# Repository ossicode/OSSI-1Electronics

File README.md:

### OSSI-1 Satellite Electronics Final Version 
#### Launched on 19th April 2013

**Check for modules for images, schematics, and BOMs.**

Mainly Eagle 6.1 / 6.5 version  
Please, see the comments from the schematic file for more information.  
Block diagram and rationale behind the design will be provided with video turorial soon.  

Open Source Satellite Initiative http://opensat.cc

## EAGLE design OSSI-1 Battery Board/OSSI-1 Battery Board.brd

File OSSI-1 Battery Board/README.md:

### OSSI-1 Satellite Battery Board

**The battery board contains Saft 144350 lithium-ion battery and two Nesscap supercapacitors.**  
**2 analog out temperature modules are attached to the battery and the supercapacitor for temp. monitoring.**

Mainly Eagle 6.1 / 6.5 version  
Please, see the comments from the schematic file for more information.  
Block diagram and rationale behind the design will be provided with video turorial soon.  

Open Source Satellite Initiative http://opensat.cc

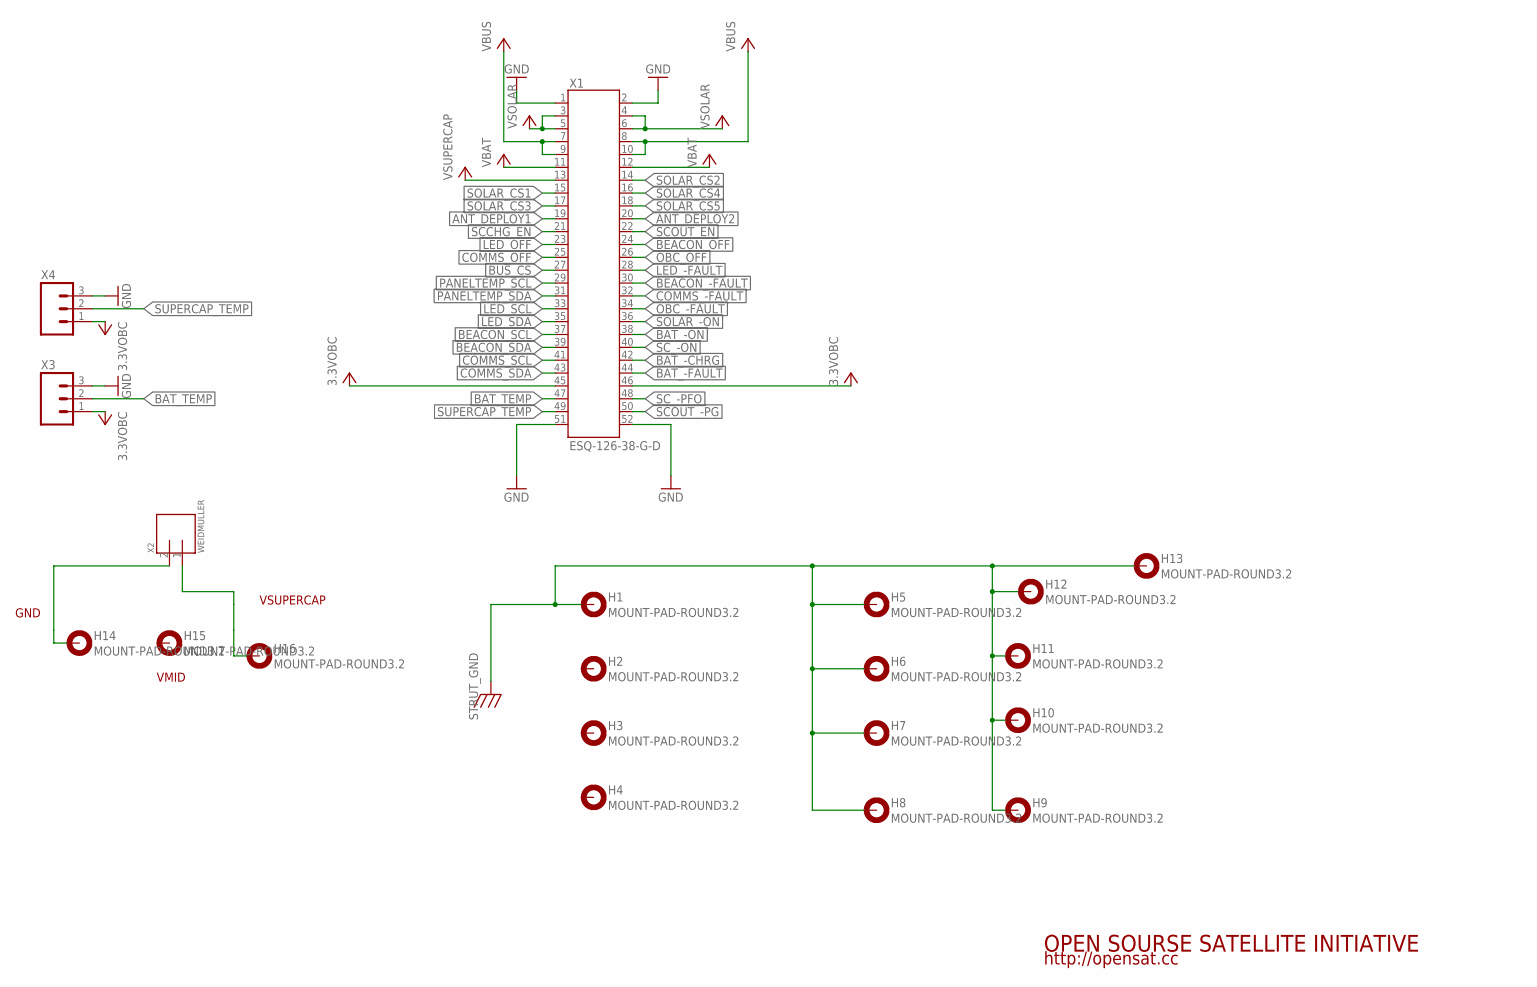
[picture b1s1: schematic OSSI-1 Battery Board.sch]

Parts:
H1, H2, H3, H4, H5, H6, H7, H8, H9, H10, H11, H12, H13, H14, H15, H16: MOUNT-PAD-ROUND3.2; 3.2-PAD-ROUND
X1: ESQ-126-38-G-D; ESQ-126-XX-X-D
X2: WEIDMULLER; WEIDMULLER1760490000
X3, X4: M03PTH; 1X03

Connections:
3.3VOBC: X1.45, X1.46, X3.1, X4.1
ANT_DEPLOY1: X1.19
ANT_DEPLOY2: X1.20
BAT_-CHRG: X1.42
BAT_-FAULT: X1.44
BAT_-ON: X1.38
BAT_TEMP: X1.47, X3.2
BEACON_-FAULT: X1.30
BEACON_OFF: X1.24
BEACON_SCL: X1.37
BEACON_SDA: X1.39
BUS_CS: X1.27
COMMS_-FAULT: X1.32
COMMS_OFF: X1.25
COMMS_SCL: X1.41
COMMS_SDA: X1.43
GND: X1.1, X1.2, X1.51, X1.52, X3.3, X4.3
LED_-FAULT: X1.28
LED_OFF: X1.23
LED_SCL: X1.33
LED_SDA: X1.35
unnamed: H14.B3,2, X2.2
unnamed: H16.B3,2, X2.1
OBC_-FAULT: X1.34
OBC_OFF: X1.26
PANELTEMP_SCL: X1.29
PANELTEMP_SDA: X1.31
SCCHG_EN: X1.21
SCOUT_-PG: X1.50
SCOUT_EN: X1.22
SC_-ON: X1.40
SC_-PFO: X1.48
SOLAR_-ON: X1.36
SOLAR_CS1: X1.15
SOLAR_CS2: X1.14
SOLAR_CS3: X1.17
SOLAR_CS4: X1.16
SOLAR_CS5: X1.18
STRUT_GND: H1.B3,2, H5.B3,2, H6.B3,2, H7.B3,2, H8.B3,2, H9.B3,2, H10.B3,2, H11.B3,2, H12.B3,2, H13.B3,2
SUPERCAP_TEMP: X1.49, X4.2
VBAT: X1.11, X1.12
VBUS: X1.7, X1.8, X1.9, X1.10
VSOLAR: X1.3, X1.4, X1.5, X1.6
VSUPERCAP: X1.13

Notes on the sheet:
GND
VSUPERCAP
VMID
OPEN SOURSE SATELLITE INITIATIVE
http://opensat.cc

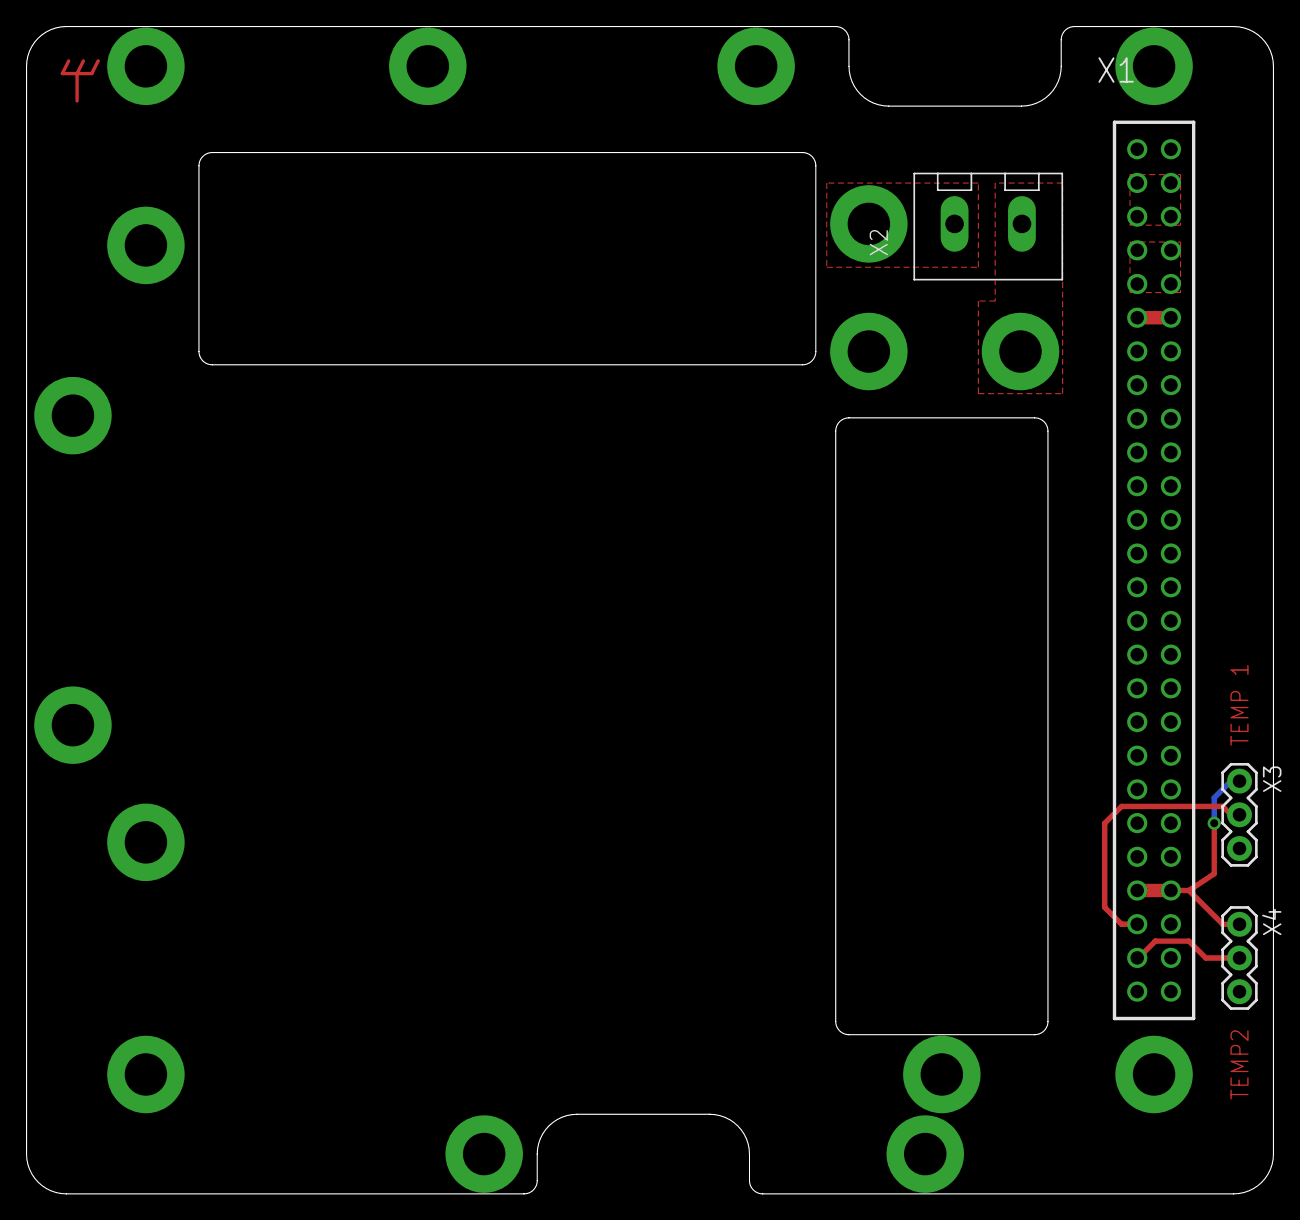
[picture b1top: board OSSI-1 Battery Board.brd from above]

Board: 2 copper layers, 94.0 x 88.0 mm, 20 parts (0 on the bottom side), 10 nets.

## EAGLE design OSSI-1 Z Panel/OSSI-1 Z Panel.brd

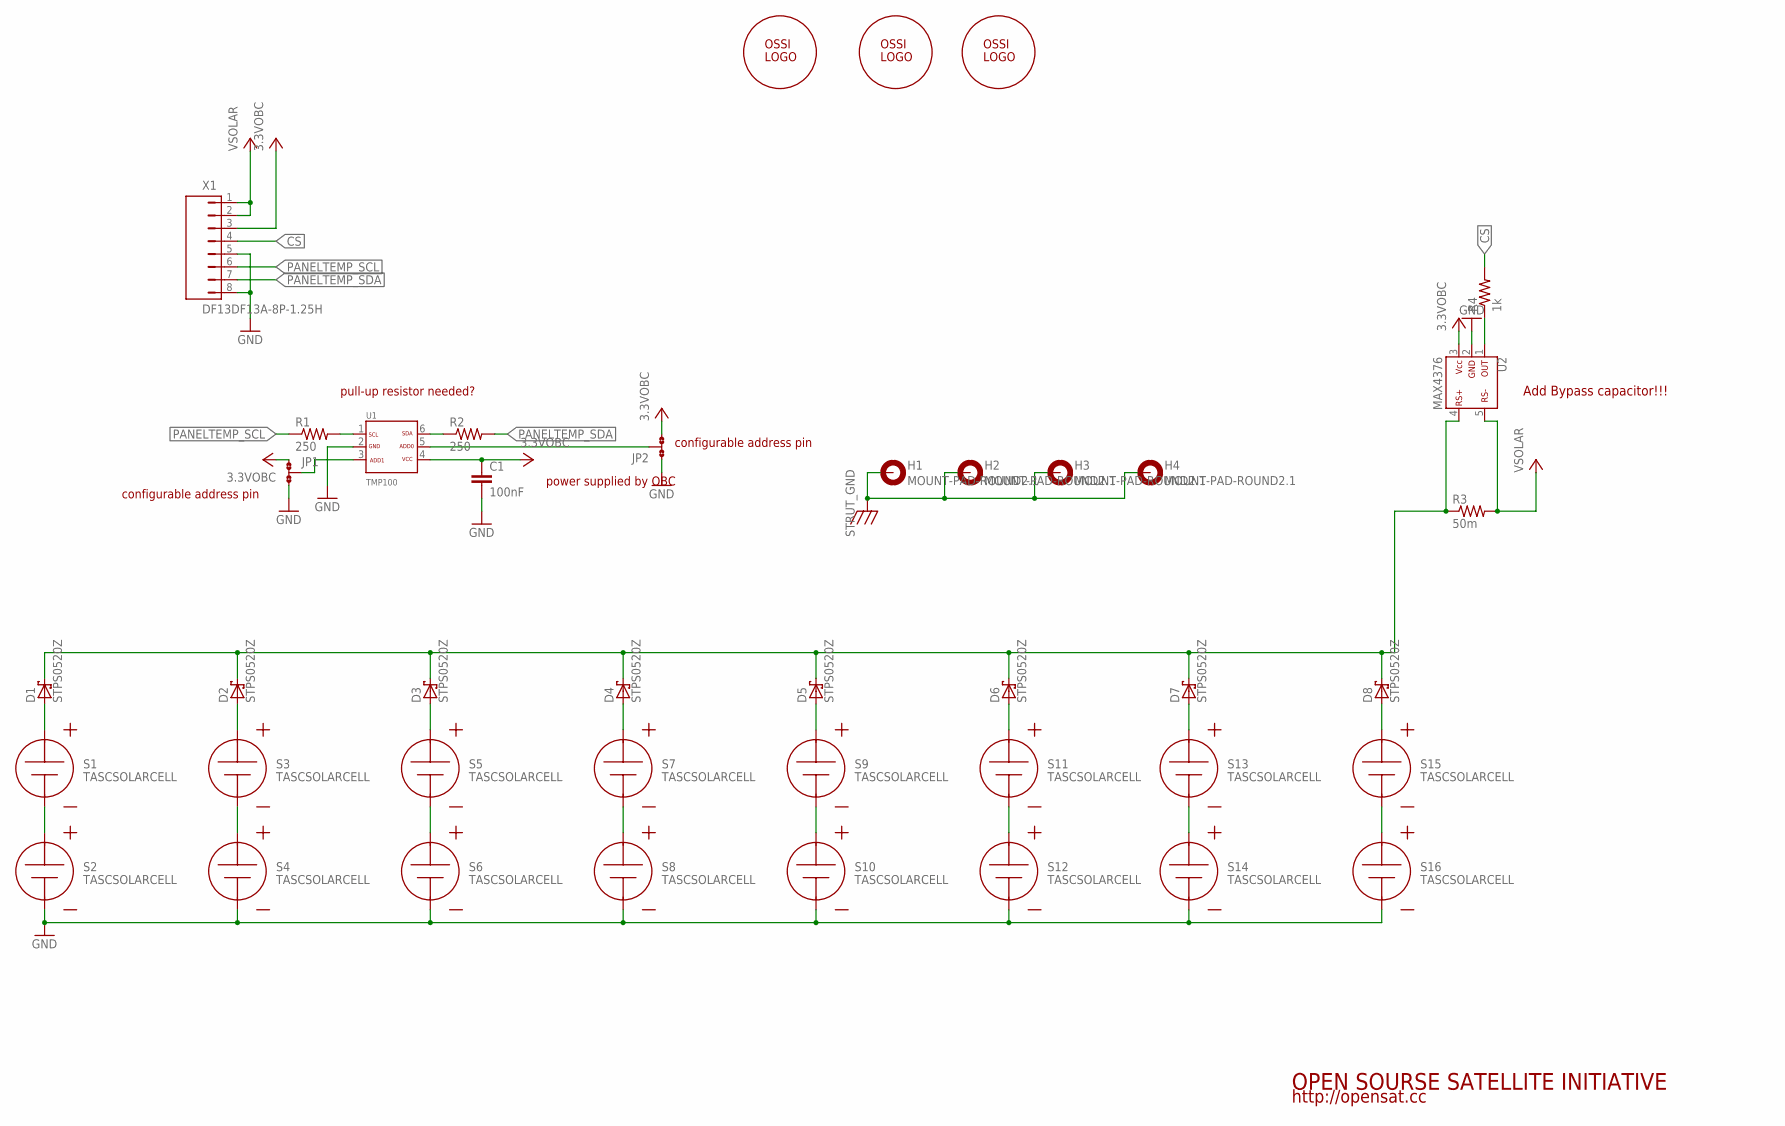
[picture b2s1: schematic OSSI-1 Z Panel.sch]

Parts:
C1: 100nF; C0603(1608)
D1, D2, D3, D4, D5, D6, D7, D8: STPS0520Z; SOD-123
H1, H2, H3, H4: MOUNT-PAD-ROUND2.1; 2.1-PAD-ROUND
JP1, JP2: JP2; JP2SMD0603
R1, R2: 250; R0603(1608)
R3: 50m; WSL1206
R4: 1k; R0603(1608)
S1, S2, S3, S4, S5, S6, S7, S8, S9, S10, S11, S12, S13, S14, S15, S16: TASCSOLARCELL
U1: TMP100; SOT23-6DBV
U2: MAX4376; SOT23-5DBV
U$1, U$2: OSSILOGO-10; OSSILOGO1010
U$3: OSSITAGCC; CCLOGO
X1: DF13DF13A-8P-1.25H; DF13A-8P

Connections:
3.3VOBC: C1.1, JP1.1, JP2.3, U1.4, U2.3, X1.3
CS: R4.2, X1.4
GND: C1.2, JP1.3, JP2.1, S2.N, S4.N, S6.N, S8.N, S10.N, S12.N, S14.N, S16.N, U1.2, U2.2, X1.5, X1.8
unnamed: S1.N, S2.P
unnamed: D1.A, S1.P
unnamed: S3.N, S4.P
unnamed: D2.A, S3.P
unnamed: S5.N, S6.P
unnamed: D3.A, S5.P
unnamed: S7.N, S8.P
unnamed: D4.A, S7.P
unnamed: S9.N, S10.P
unnamed: D5.A, S9.P
unnamed: S11.N, S12.P
unnamed: D6.A, S11.P
unnamed: S13.N, S14.P
unnamed: D7.A, S13.P
unnamed: S15.N, S16.P
unnamed: D8.A, S15.P
unnamed: R1.2, U1.1
unnamed: R2.1, U1.6
unnamed: D1.C, D2.C, D3.C, D4.C, D5.C, D6.C, D7.C, D8.C, R3.P$1 (1), U2.4
unnamed: JP1.2, U1.3
unnamed: JP2.2, U1.5
unnamed: R4.1, U2.1
PANELTEMP_SCL: R1.1, X1.6
PANELTEMP_SDA: R2.2, X1.7
STRUT_GND: H1.B3,2, H2.B3,2, H3.B3,2, H4.B3,2
VSOLAR: R3.P$2 (2), U2.5, X1.1, X1.2

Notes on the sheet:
configurable address pin
pull-up resistor needed?
power supplied by OBC
Add Bypass capacitor!!!
OPEN SOURSE SATELLITE INITIATIVE
http://opensat.cc

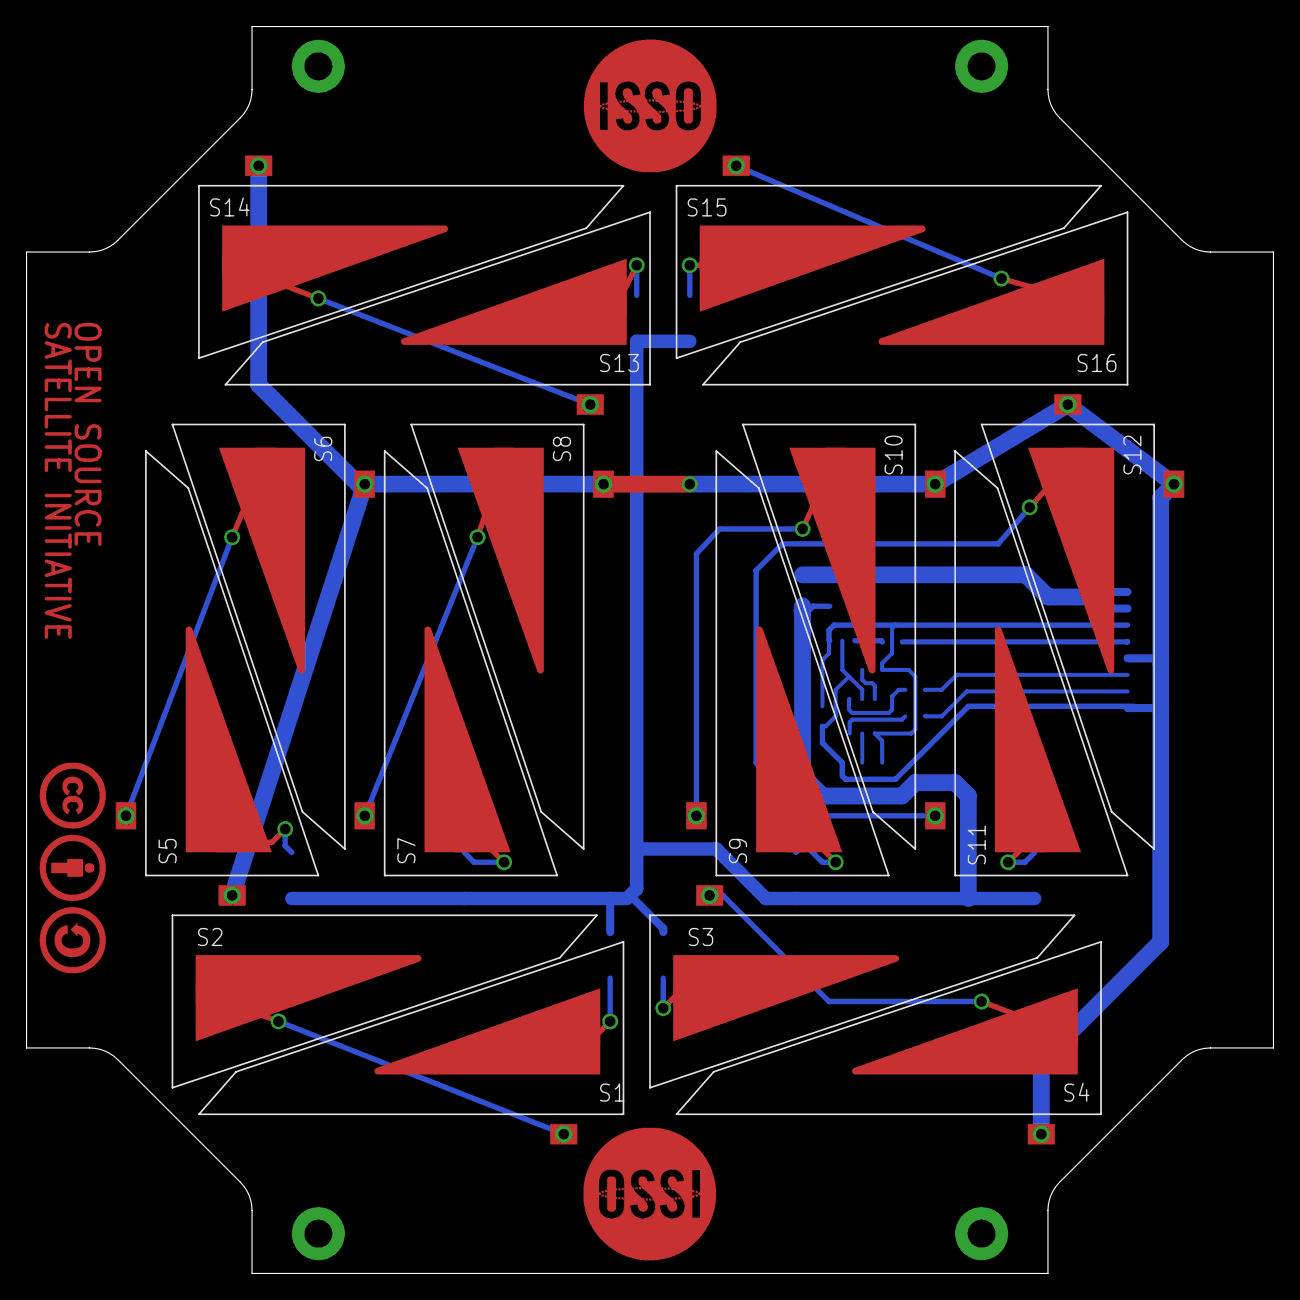
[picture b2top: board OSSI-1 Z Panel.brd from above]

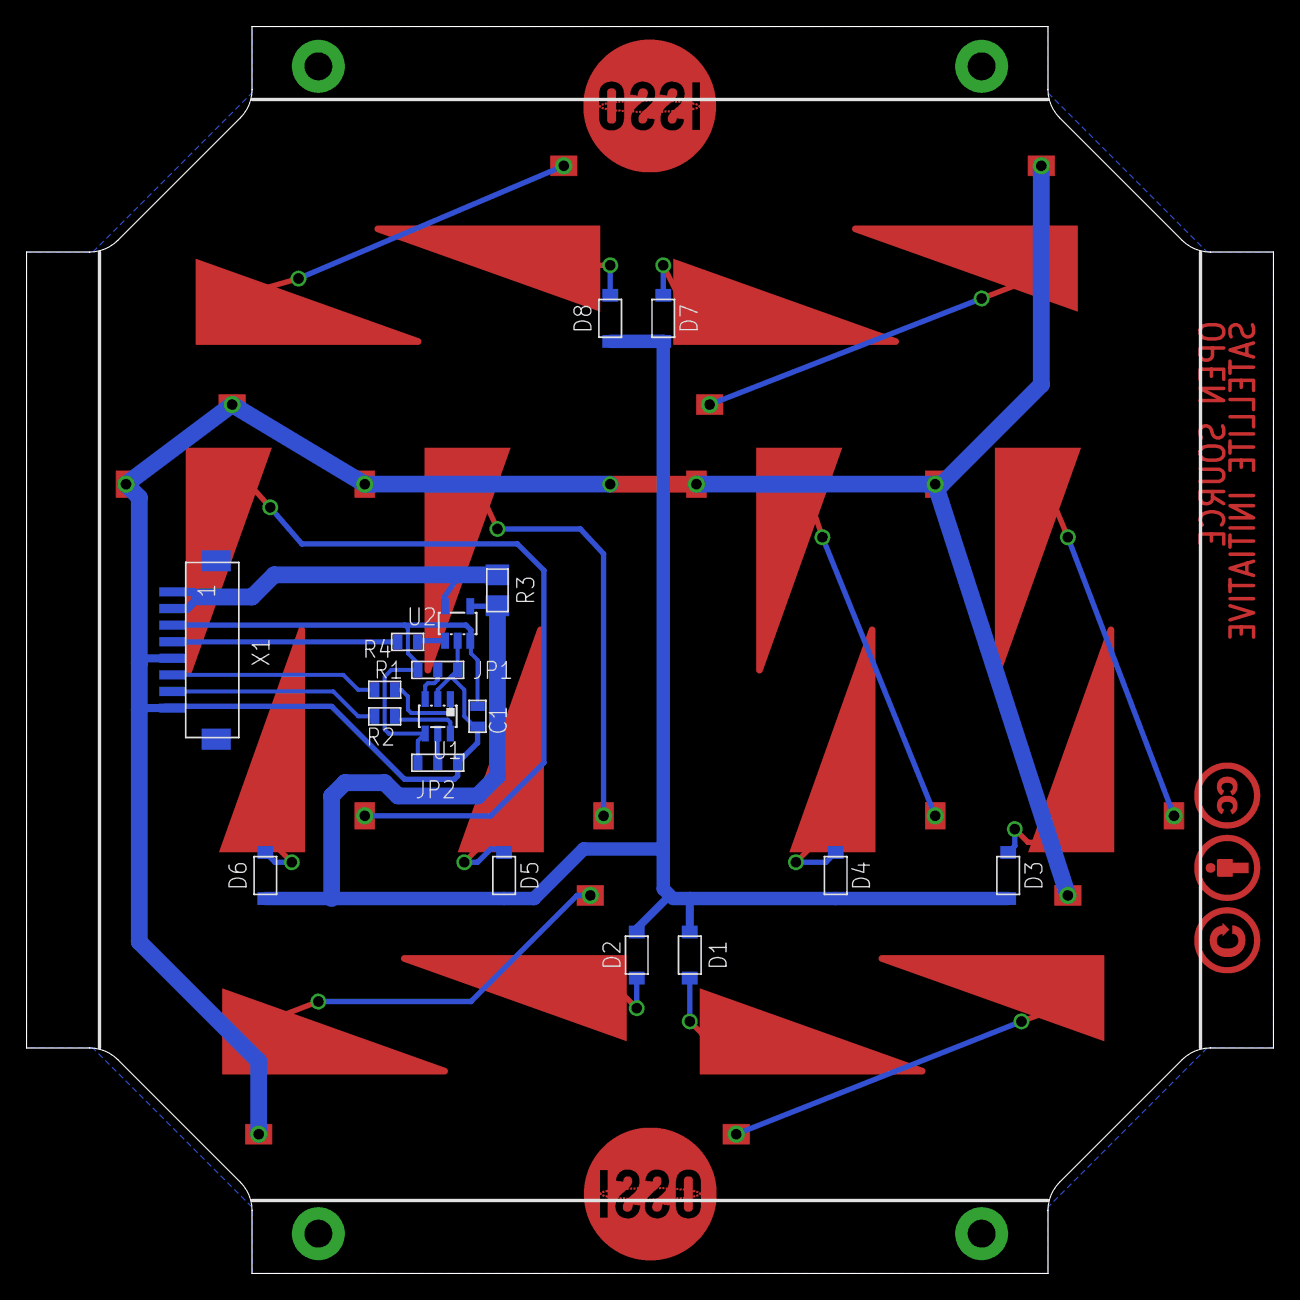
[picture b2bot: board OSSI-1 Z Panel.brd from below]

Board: 2 copper layers, 94.0 x 94.0 mm, 41 parts (18 on the bottom side), 29 nets.

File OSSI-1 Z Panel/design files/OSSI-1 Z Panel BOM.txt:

Part	Value	Attributes	Package	Description	Part Num
C1	100nF		C0603(1608)		*
D1	STPS0520Z		SOD-123	We use STPS0520Z by st.com diode for solar cell schottky diode.	*
D2	STPS0520Z		SOD-123	We use STPS0520Z by st.com diode for solar cell schottky diode.	*
D3	STPS0520Z		SOD-123	We use STPS0520Z by st.com diode for solar cell schottky diode.	*
D4	STPS0520Z		SOD-123	We use STPS0520Z by st.com diode for solar cell schottky diode.	*
D5	STPS0520Z		SOD-123	We use STPS0520Z by st.com diode for solar cell schottky diode.	*
D6	STPS0520Z		SOD-123	We use STPS0520Z by st.com diode for solar cell schottky diode.	*
D7	STPS0520Z		SOD-123	We use STPS0520Z by st.com diode for solar cell schottky diode.	*
D8	STPS0520Z		SOD-123	We use STPS0520Z by st.com diode for solar cell schottky diode.	*
H1	MOUNT-PAD-ROUND2.1		2.1-PAD-ROUND		*
H2	MOUNT-PAD-ROUND2.1		2.1-PAD-ROUND		*
H3	MOUNT-PAD-ROUND2.1		2.1-PAD-ROUND		*
H4	MOUNT-PAD-ROUND2.1		2.1-PAD-ROUND		*
JP1	JP2		JP2SMD0603		*
JP2	JP2		JP2SMD0603		*
R1	250		R0603(1608)		*
R2	250		R0603(1608)		*
R3	50m		WSL1206		*
R4	1k		R0603(1608)		*
S1	TASCSOLARCELL		TASCSOLARCELL		*
S2	TASCSOLARCELL		TASCSOLARCELL		*
S3	TASCSOLARCELL		TASCSOLARCELL		*
S4	TASCSOLARCELL		TASCSOLARCELL		*
S5	TASCSOLARCELL		TASCSOLARCELL		*
S6	TASCSOLARCELL		TASCSOLARCELL		*
S7	TASCSOLARCELL		TASCSOLARCELL		*
S8	TASCSOLARCELL		TASCSOLARCELL		*
S9	TASCSOLARCELL		TASCSOLARCELL		*
S10	TASCSOLARCELL		TASCSOLARCELL		*
S11	TASCSOLARCELL		TASCSOLARCELL		*
S12	TASCSOLARCELL		TASCSOLARCELL		*
S13	TASCSOLARCELL		TASCSOLARCELL		*
S14	TASCSOLARCELL		TASCSOLARCELL		*
S15	TASCSOLARCELL		TASCSOLARCELL		*
S16	TASCSOLARCELL		TASCSOLARCELL		*
U$1	OSSILOGO-10		OSSILOGO1010		*
U$2	OSSILOGO-10		OSSILOGO1010		*
U$3	OSSITAGCC		CCLOGO		*
U1	TMP100		SOT23-6DBV	TMP100 Digital Temerature Sensor with I2C Interface from Texas Instruments	*
U2	MAX4376		SOT23-5DBV		*
X1	DF13DF13A-8P-1.25H		DF13A-8P	Hirose DF13 series connector	*

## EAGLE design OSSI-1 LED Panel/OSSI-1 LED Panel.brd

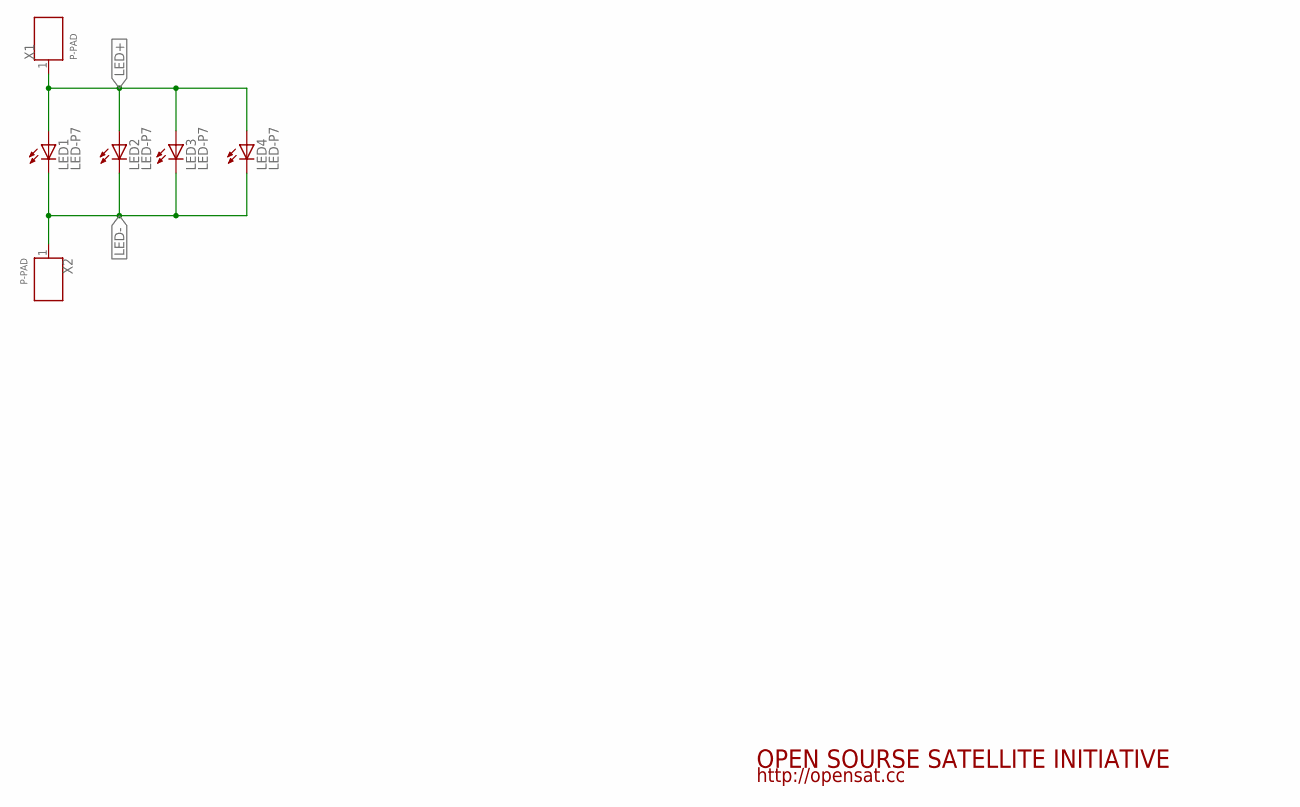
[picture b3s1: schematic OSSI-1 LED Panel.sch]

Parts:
LED1, LED2, LED3, LED4: LED-P7; P7
X1, X2: P-PAD

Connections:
LED+: LED1.A, LED2.A, LED3.A, LED4.A, X1.1
LED-: LED1.C, LED2.C, LED3.C, LED4.C, X2.1

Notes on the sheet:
OPEN SOURSE SATELLITE INITIATIVE
http://opensat.cc

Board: 2 copper layers, 6 parts (0 on the bottom side), 2 nets, no tracks yet.

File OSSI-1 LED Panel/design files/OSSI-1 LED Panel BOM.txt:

Part	Value	Attributes	Package	Description	Part Num
LED1	LED-P7		P7		*
LED2	LED-P7		P7		*
LED3	LED-P7		P7		*
LED4	LED-P7		P7		*
X1	P-PAD		P-PAD		*
X2	P-PAD		P-PAD		*

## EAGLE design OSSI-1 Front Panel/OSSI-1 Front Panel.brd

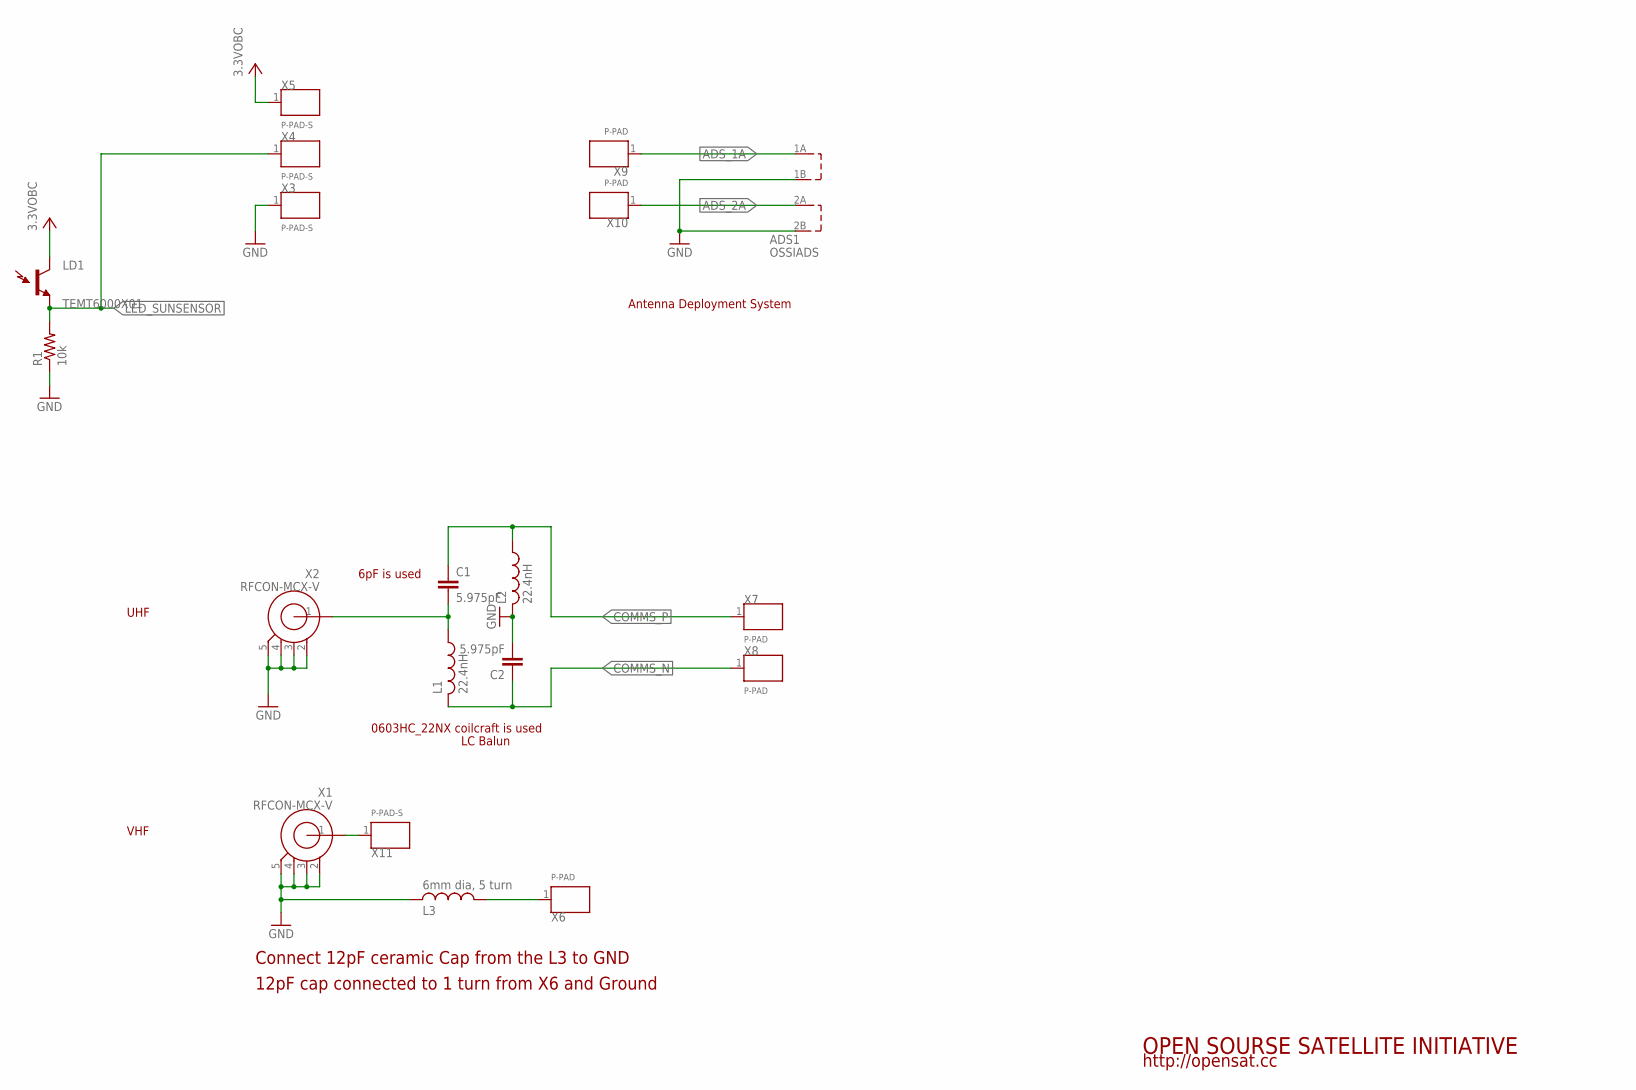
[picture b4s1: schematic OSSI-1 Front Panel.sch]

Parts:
ADS1: OSSIADS
C1, C2: 5.975pF; C0805(2012)
L1, L2: 22.4nH; L0805(2012)
L3: 6mm dia, 5 turn; 0207/10
LD1: TEMT6000X01; TEMT6000-SEN
R1: 10k; R0805(2012)
X1, X2: RFCON-MCX-V; MCX-V
X3, X4, X5, X11: P-PAD-S
X6, X7, X8, X9, X10: P-PAD

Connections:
3.3VOBC: LD1.COLLECTOR (C1), X5.1
ADS_1A: ADS1.1A, X9.1
ADS_2A: ADS1.2A, X10.1
COMMS_N: C2.1, L1.2, X8.1
COMMS_P: C1.1, L2.1, X7.1
GND: ADS1.1B, ADS1.2B, C2.2, L2.2, L3.2, R1.1, X1.2, X1.3, X1.4, X1.5, X2.2, X2.3, X2.4, X2.5, X3.1
LED_SUNSENSOR: LD1.EMITTER (E1), R1.2, X4.1
unnamed: L3.1, X6.1
unnamed: X1.1, X11.1
unnamed: C1.2, L1.1, X2.1

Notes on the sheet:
LC Balun
0603HC_22NX coilcraft is used
6pF is used
UHF
VHF
Antenna Deployment System
Connect 12pF ceramic Cap from the L3 to GND
12pF cap connected to 1 turn from X6 and Ground
OPEN SOURSE SATELLITE INITIATIVE
http://opensat.cc

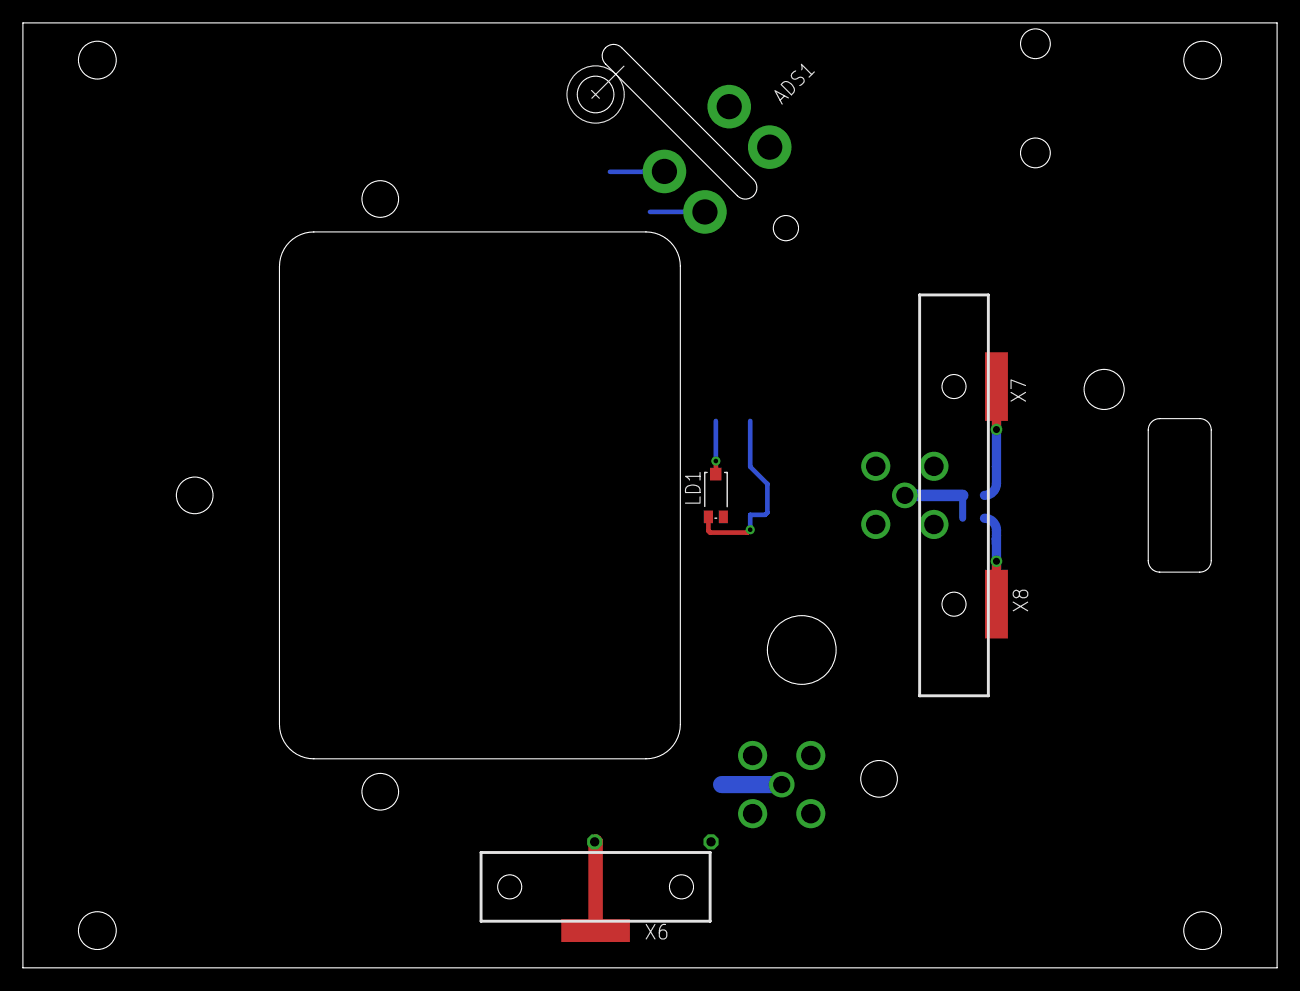
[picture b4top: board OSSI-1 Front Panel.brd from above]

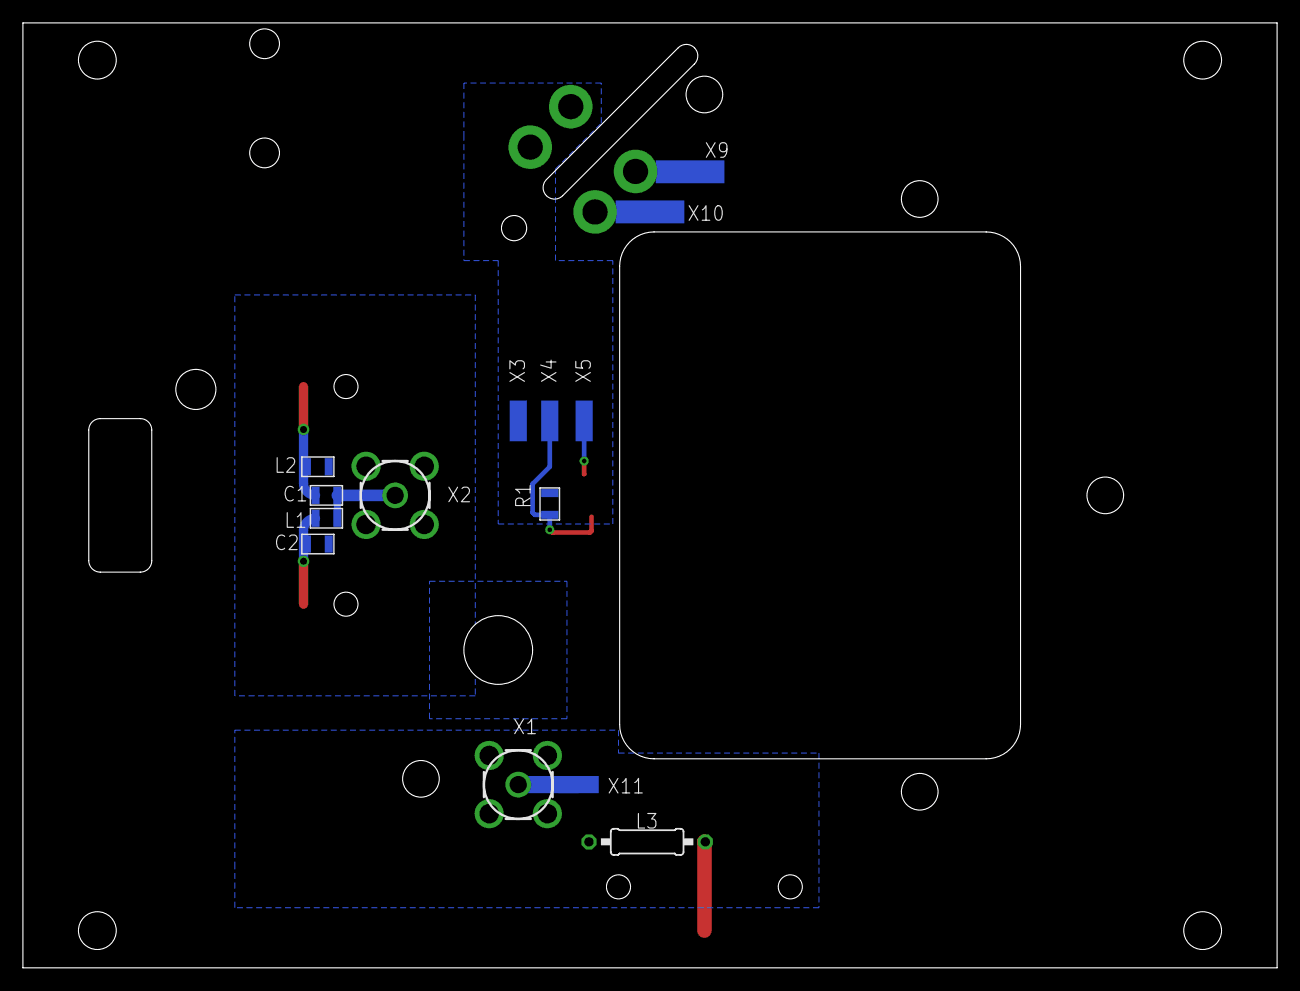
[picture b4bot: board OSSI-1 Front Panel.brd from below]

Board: 2 copper layers, 109.5 x 82.5 mm, 19 parts (14 on the bottom side), 10 nets.

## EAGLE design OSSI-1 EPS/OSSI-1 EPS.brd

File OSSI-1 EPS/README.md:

### OSSI-1 Satellite EPS

**EPS is the power supply board for the satellite.** 
**Multiple power sources are OR-ed by ideal diodes for reliabilty.**

Mainly Eagle 6.1 / 6.5 version  
Please, see the comments from the schematic file for more information.  
Block diagram and rationale behind the design will be provided with video turorial soon.  

Open Source Satellite Initiative http://opensat.cc

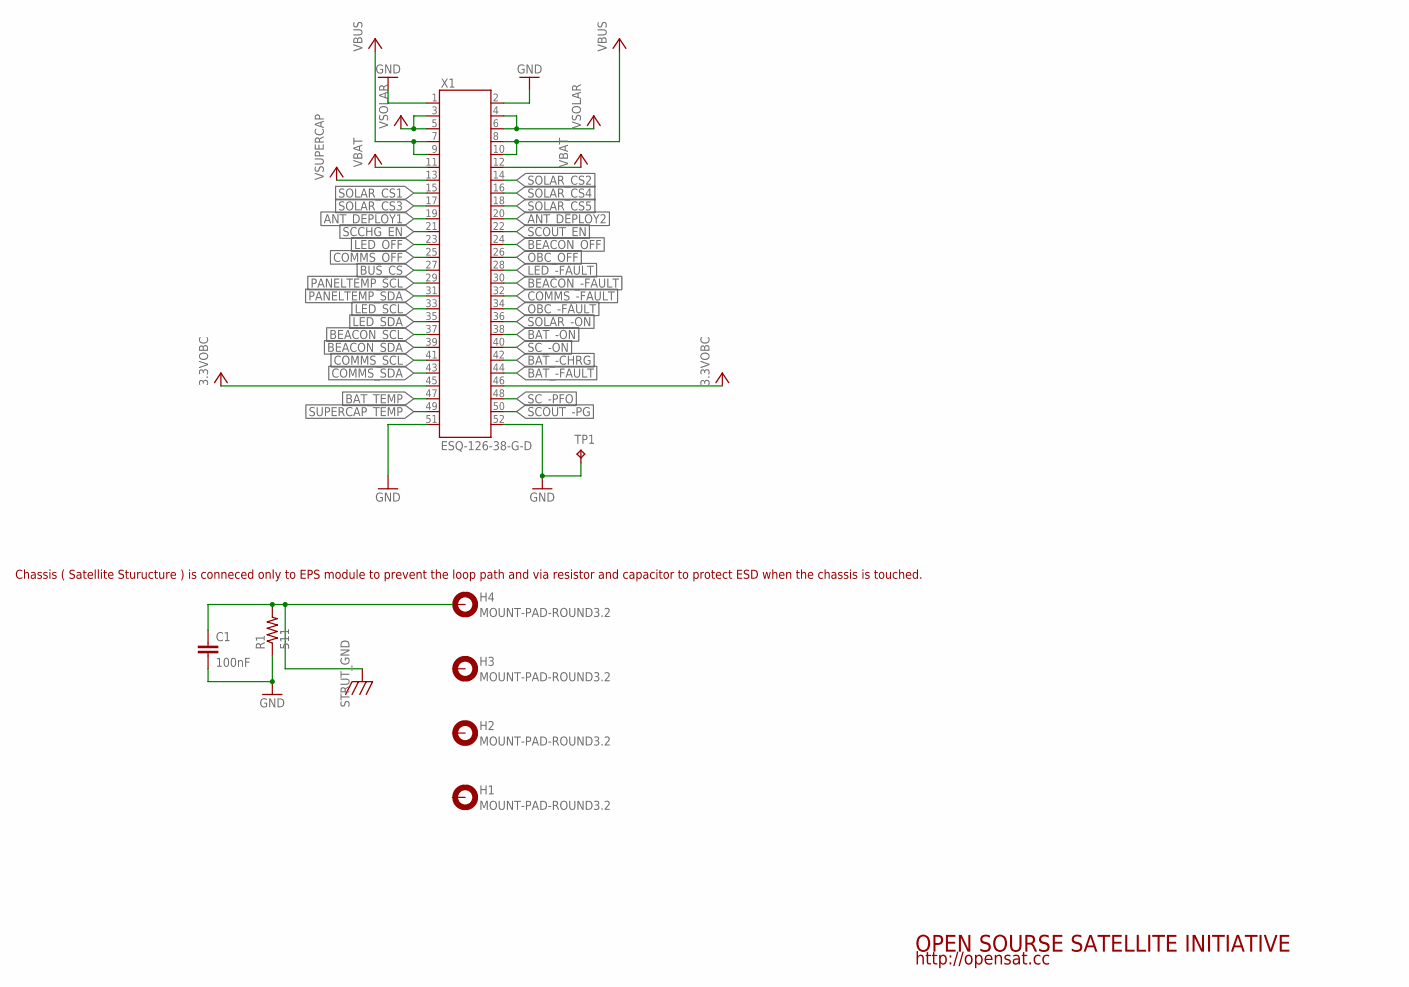
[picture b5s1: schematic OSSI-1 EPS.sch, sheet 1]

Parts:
C1: 100nF; C0805(2012)
H1, H2, H3, H4: MOUNT-PAD-ROUND3.2; 3.2-PAD-ROUND
R1: 511; WSL1206
TP1: TP; TP-13
X1: ESQ-126-38-G-D; ESQ-126-XX-X-D

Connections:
3.3VOBC: X1.45, X1.46; also elsewhere on the board
ANT_DEPLOY1: X1.19; also elsewhere on the board
ANT_DEPLOY2: X1.20; also elsewhere on the board
BAT_-CHRG: X1.42; also elsewhere on the board
BAT_-FAULT: X1.44; also elsewhere on the board
BAT_-ON: X1.38; also elsewhere on the board
BAT_TEMP: X1.47
BEACON_-FAULT: X1.30
BEACON_OFF: X1.24
BEACON_SCL: X1.37
BEACON_SDA: X1.39
BUS_CS: X1.27; also elsewhere on the board
COMMS_-FAULT: X1.32
COMMS_OFF: X1.25
COMMS_SCL: X1.41
COMMS_SDA: X1.43
GND: C1.2, R1.P$1 (1), TP1.TP, X1.1, X1.2, X1.51, X1.52; also elsewhere on the board
LED_-FAULT: X1.28
LED_OFF: X1.23
LED_SCL: X1.33
LED_SDA: X1.35
OBC_-FAULT: X1.34
OBC_OFF: X1.26
PANELTEMP_SCL: X1.29
PANELTEMP_SDA: X1.31
SCCHG_EN: X1.21; also elsewhere on the board
SCOUT_-PG: X1.50
SCOUT_EN: X1.22; also elsewhere on the board
SC_-ON: X1.40; also elsewhere on the board
SC_-PFO: X1.48; also elsewhere on the board
SOLAR_-ON: X1.36; also elsewhere on the board
SOLAR_CS1: X1.15
SOLAR_CS2: X1.14
SOLAR_CS3: X1.17
SOLAR_CS4: X1.16
SOLAR_CS5: X1.18
STRUT_GND: C1.1, H4.B3,2, R1.P$2 (2)
SUPERCAP_TEMP: X1.49
VBAT: X1.11, X1.12; also elsewhere on the board
VBUS: X1.7, X1.8, X1.9, X1.10; also elsewhere on the board
VSOLAR: X1.3, X1.4, X1.5, X1.6; also elsewhere on the board
VSUPERCAP: X1.13; also elsewhere on the board

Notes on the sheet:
Chassis ( Satellite Sturucture ) is conneced only to EPS module to prevent the loop path and via resistor and capacitor to protect ESD when the chassis is touched.
OPEN SOURSE SATELLITE INITIATIVE
http://opensat.cc

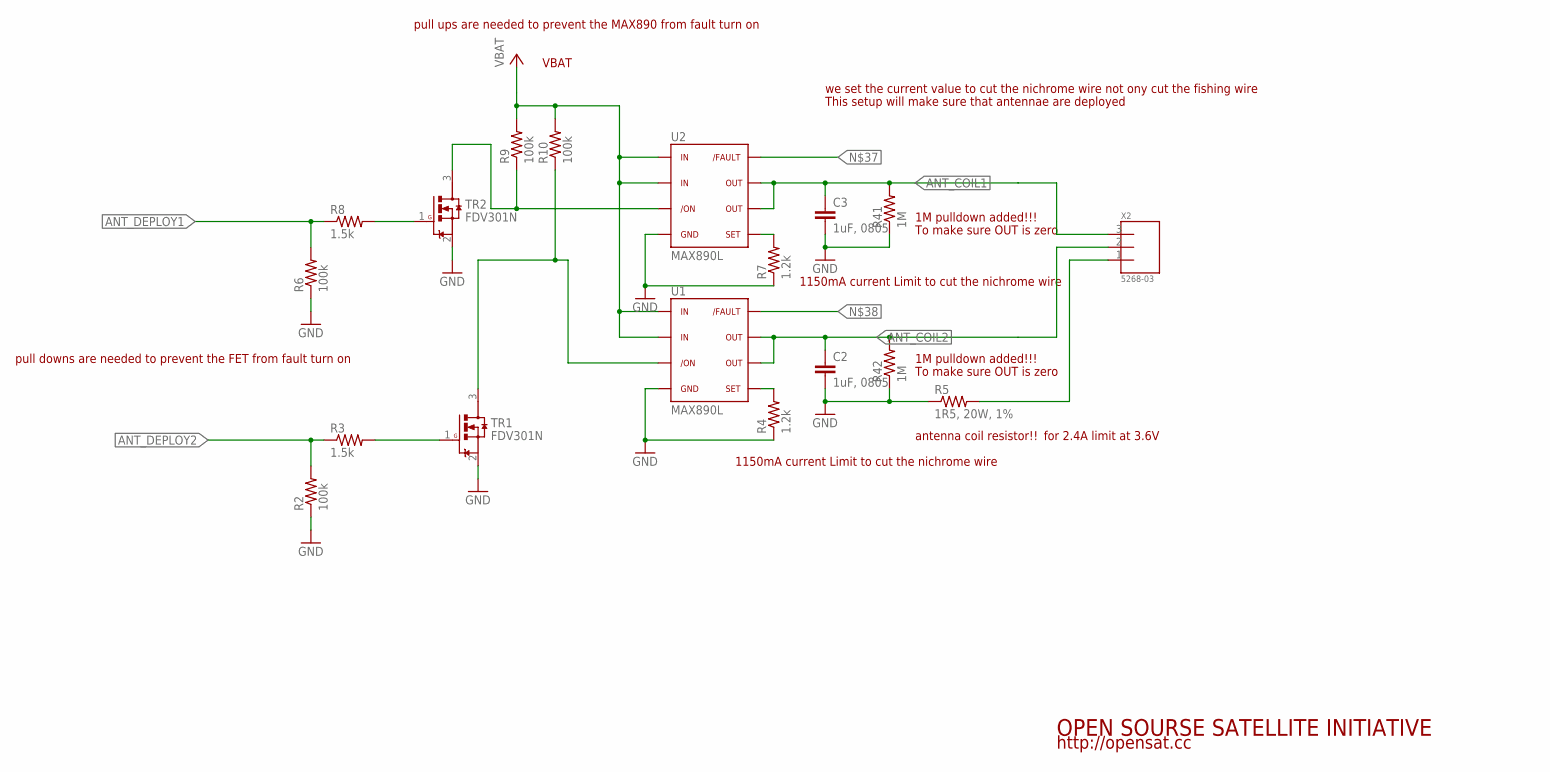
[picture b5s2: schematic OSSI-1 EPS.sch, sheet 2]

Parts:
C2, C3: 1uF, 0805; C0805(2012)
R2, R6, R9, R10: 100k; R0603(1608)
R3, R8: 1.5k; R0603(1608)
R4, R7: 1.2k; R0603(1608)
R5: 1R5, 20W, 1%; PWR263S-20
R41, R42: 1M; R0603(1608)
TR1, TR2: FDV301N; SOT23
U1, U2: MAX890L; SO8
X2: 5268-03

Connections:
ANT_COIL1: C3.1, R41.2, U2.6, U2.7, X2.3
ANT_COIL2: C2.1, R42.2, U1.6, U1.7, X2.2
ANT_DEPLOY1: R6.2, R8.1; also elsewhere on the board
ANT_DEPLOY2: R2.2, R3.1; also elsewhere on the board
GND: C2.2, C3.2, R2.1, R4.1, R5.P$1 (1), R6.1, R7.1, R41.1, R42.1, TR1.2 (S), TR2.2 (S), U1.4, U2.4; also elsewhere on the board
unnamed: R3.2, TR1.1 (G)
unnamed: R8.2, TR2.1 (G)
unnamed: R9.1, TR2.3 (D), U2.3
unnamed: R10.1, TR1.3 (D), U1.3
unnamed: R7.2, U2.5
unnamed: R4.2, U1.5
unnamed: R5.P$2 (2), X2.1
VBAT: R9.2, R10.2, U1.1, U1.2, U2.1, U2.2; also elsewhere on the board

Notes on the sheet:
VBAT
antenna coil resistor!!
1150mA current Limit to cut the nichrome wire
for 2.4A limit at 3.6V
1M pulldown added!!!
To make sure OUT is zero
pull downs are needed to prevent the FET from fault turn on
pull ups are needed to prevent the MAX890 from fault turn on
we set the current value to cut the nichrome wire not ony cut the fishing wire
This setup will make sure that antennae are deployed
OPEN SOURSE SATELLITE INITIATIVE
http://opensat.cc

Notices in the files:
parts and their libraries:
SparkFun: Licensing: CC v3.0 Share-Alike You are welcome to use this library for commercial purposes.
